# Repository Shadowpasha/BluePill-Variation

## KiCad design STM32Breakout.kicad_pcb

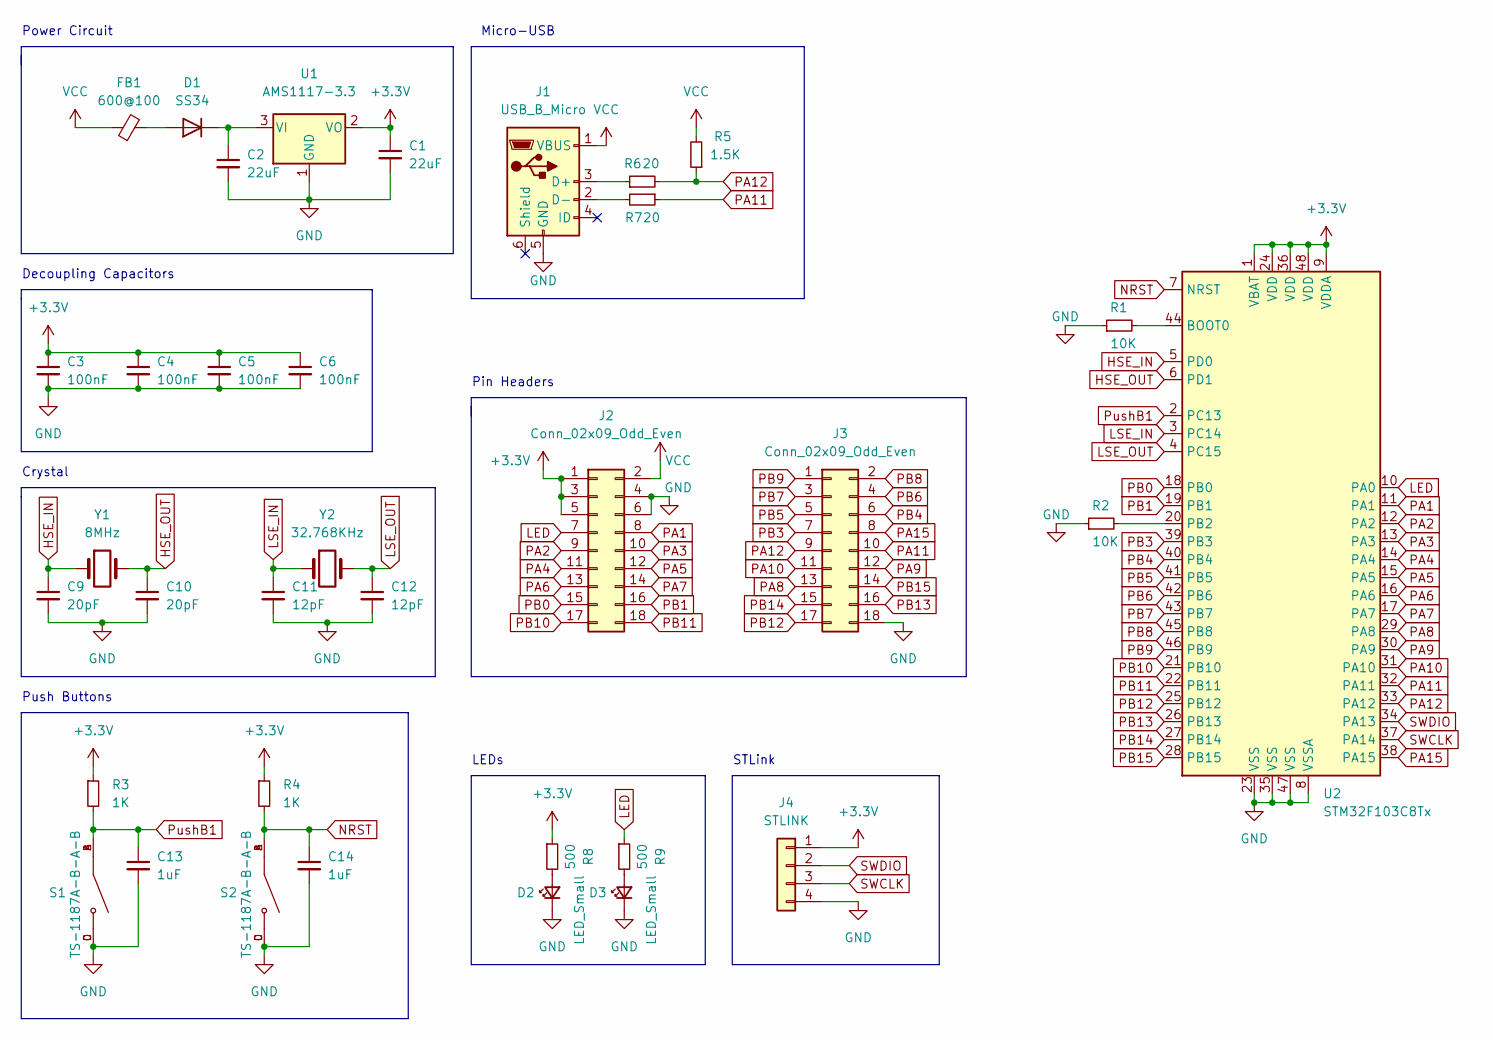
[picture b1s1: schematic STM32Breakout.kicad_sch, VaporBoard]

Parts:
C1, C2: 22uF; C_1206_3216Metric
C3, C4, C5, C6: 100nF; C_0402_1005Metric
C9, C10: 20pF; C_0402_1005Metric
C11, C12: 12pF; C_0402_1005Metric
C13, C14: 1uF; C_0402_1005Metric
D1: SS34; D_SOD-123
D2: LED_Small; LED_0805_2012Metric
D3: LED_Small; LED_0603_1608Metric
FB1: 600@100; L_0805_2012Metric
J1: USB_B_Micro; USB_Micro-B_Molex-105017-0001
J2, J3: Conn_02x09_Odd_Even; PinHeader_2x09_P2.54mm_Vertical
J4: STLINK; PinHeader_1x04_P2.54mm_Vertical
R1, R2: 10K; R_0402_1005Metric
R3, R4: 1K; R_0402_1005Metric
R5: 1.5K; R_0402_1005Metric
R6, R7: 20; R_0402_1005Metric
R8, R9: 500; R_0402_1005Metric
S1, S2: TS-1187A-B-A-B; SW_TS-1187A-B-A-B; PARTREV A0
U1: AMS1117-3.3; SOT-223-3_TabPin2
U2: STM32F103C8Tx; LQFP-48_7x7mm_P0.5mm
Y1: 8MHz; Crystal_SMD_5032-2Pin_5.0x3.2mm
Y2: 32.768KHz; Crystal_SMD_3215-2Pin_3.2x1.5mm

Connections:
+3.3V: C1.1, C3.1, C4.1, C5.1, C6.1, J2.1, J2.3, J2.5, J4.1, R3.1, R4.1, R8.1, U1.2 (VO), U2.1 (VBAT), U2.9 (VDDA), U2.24 (VDD), U2.36 (VDD), U2.48 (VDD)
GND: C1.2, C2.2, C3.2, C4.2, C5.2, C6.2, C9.2, C10.2, C11.2, C12.2, C13.2, C14.2, D2.1 (K), D3.1 (K), J1.5 (GND), J2.4, J2.6, J3.18, J4.4, R1.1, R2.1, S1.C, S1.D, S2.C, S2.D, U1.1 (GND), U2.8 (VSSA), U2.23 (VSS), U2.35 (VSS), U2.47 (VSS)
HSE_IN: C9.1, U2.5 (PD0), Y1.1
HSE_OUT: C10.1, U2.6 (PD1), Y1.2
LED: J2.7, R9.1, U2.10 (PA0)
LSE_IN: C11.1, U2.3 (PC14), Y2.1
LSE_OUT: C12.1, U2.4 (PC15), Y2.2
NRST: C14.1, R4.2, S2.A, S2.B, U2.7 (NRST)
unnamed: C2.1, D1.1 (K), U1.3 (VI)
unnamed: D1.2 (A), FB1.2
unnamed: D2.2 (A), R8.2
unnamed: D3.2 (A), R9.2
unnamed: J1.2 (D-), R7.2
unnamed: J1.3 (D+), R6.1
unnamed: R1.2, U2.44 (BOOT0)
unnamed: R2.2, U2.20 (PB2)
PA1: J2.8, U2.11 (PA1)
PA2: J2.9, U2.12 (PA2)
PA3: J2.10, U2.13 (PA3)
PA4: J2.11, U2.14 (PA4)
PA5: J2.12, U2.15 (PA5)
PA6: J2.13, U2.16 (PA6)
PA7: J2.14, U2.17 (PA7)
PA8: J3.13, U2.29 (PA8)
PA9: J3.12, U2.30 (PA9)
PA10: J3.11, U2.31 (PA10)
PA11: J3.10, R7.1, U2.32 (PA11)
PA12: J3.9, R5.1, R6.2, U2.33 (PA12)
PA15: J3.8, U2.38 (PA15)
PB0: J2.15, U2.18 (PB0)
PB1: J2.16, U2.19 (PB1)
PB3: J3.7, U2.39 (PB3)
PB4: J3.6, U2.40 (PB4)
PB5: J3.5, U2.41 (PB5)
PB6: J3.4, U2.42 (PB6)
PB7: J3.3, U2.43 (PB7)
PB8: J3.2, U2.45 (PB8)
PB9: J3.1, U2.46 (PB9)
PB10: J2.17, U2.21 (PB10)
PB11: J2.18, U2.22 (PB11)
PB12: J3.17, U2.25 (PB12)
PB13: J3.16, U2.26 (PB13)
PB14: J3.15, U2.27 (PB14)
PB15: J3.14, U2.28 (PB15)
PushB1: C13.1, R3.2, S1.A, S1.B, U2.2 (PC13)
SWCLK: J4.3, U2.37 (PA14)
SWDIO: J4.2, U2.34 (PA13)
VCC: FB1.1, J1.1 (VBUS), J2.2, R5.2

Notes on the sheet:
Decoupling Capacitors
Push Buttons
Micro-USB
LEDs
Crystal
STLink
Pin Headers
Power Circuit

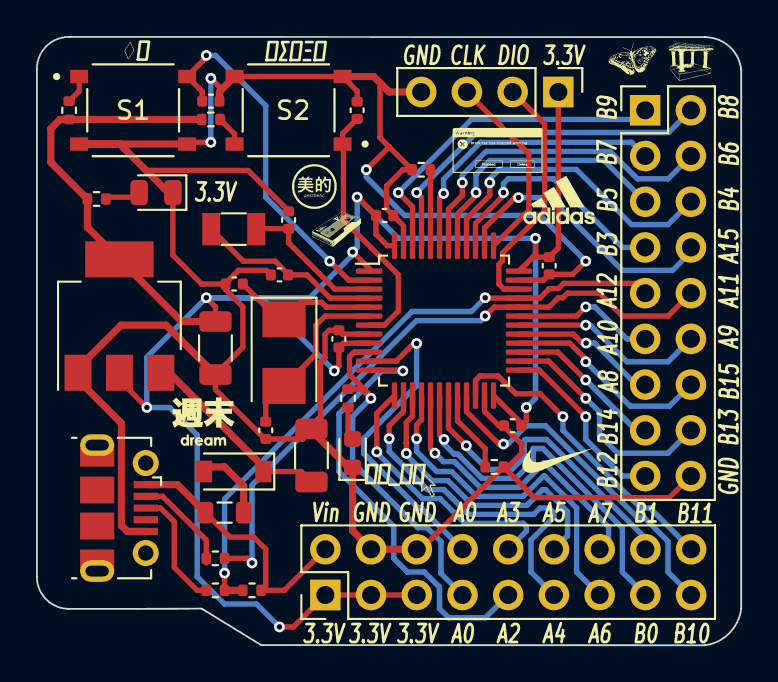
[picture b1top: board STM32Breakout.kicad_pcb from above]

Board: 2 copper layers, 39.1 x 33.8 mm, 35 parts (0 on the bottom side), 48 nets.

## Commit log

2022-12-15 Bluepill Variation
